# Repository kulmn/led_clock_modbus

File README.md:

# Clock with temperature sensor and wireless modbus protocol.

Hardware: 
- Schematic diagram (Autodesk EAGLE) in /schematic/ dir
- MCU: STM32F030K6
- Wireless: HC-12 module (433MHz)
- RTC: DS1338-33
- Indicator: 2.3 inch 7 segment led ( CA pin 1,5)

Firmvare:
- GCC Eclipse project, FreeRTOS, LibopenCM3

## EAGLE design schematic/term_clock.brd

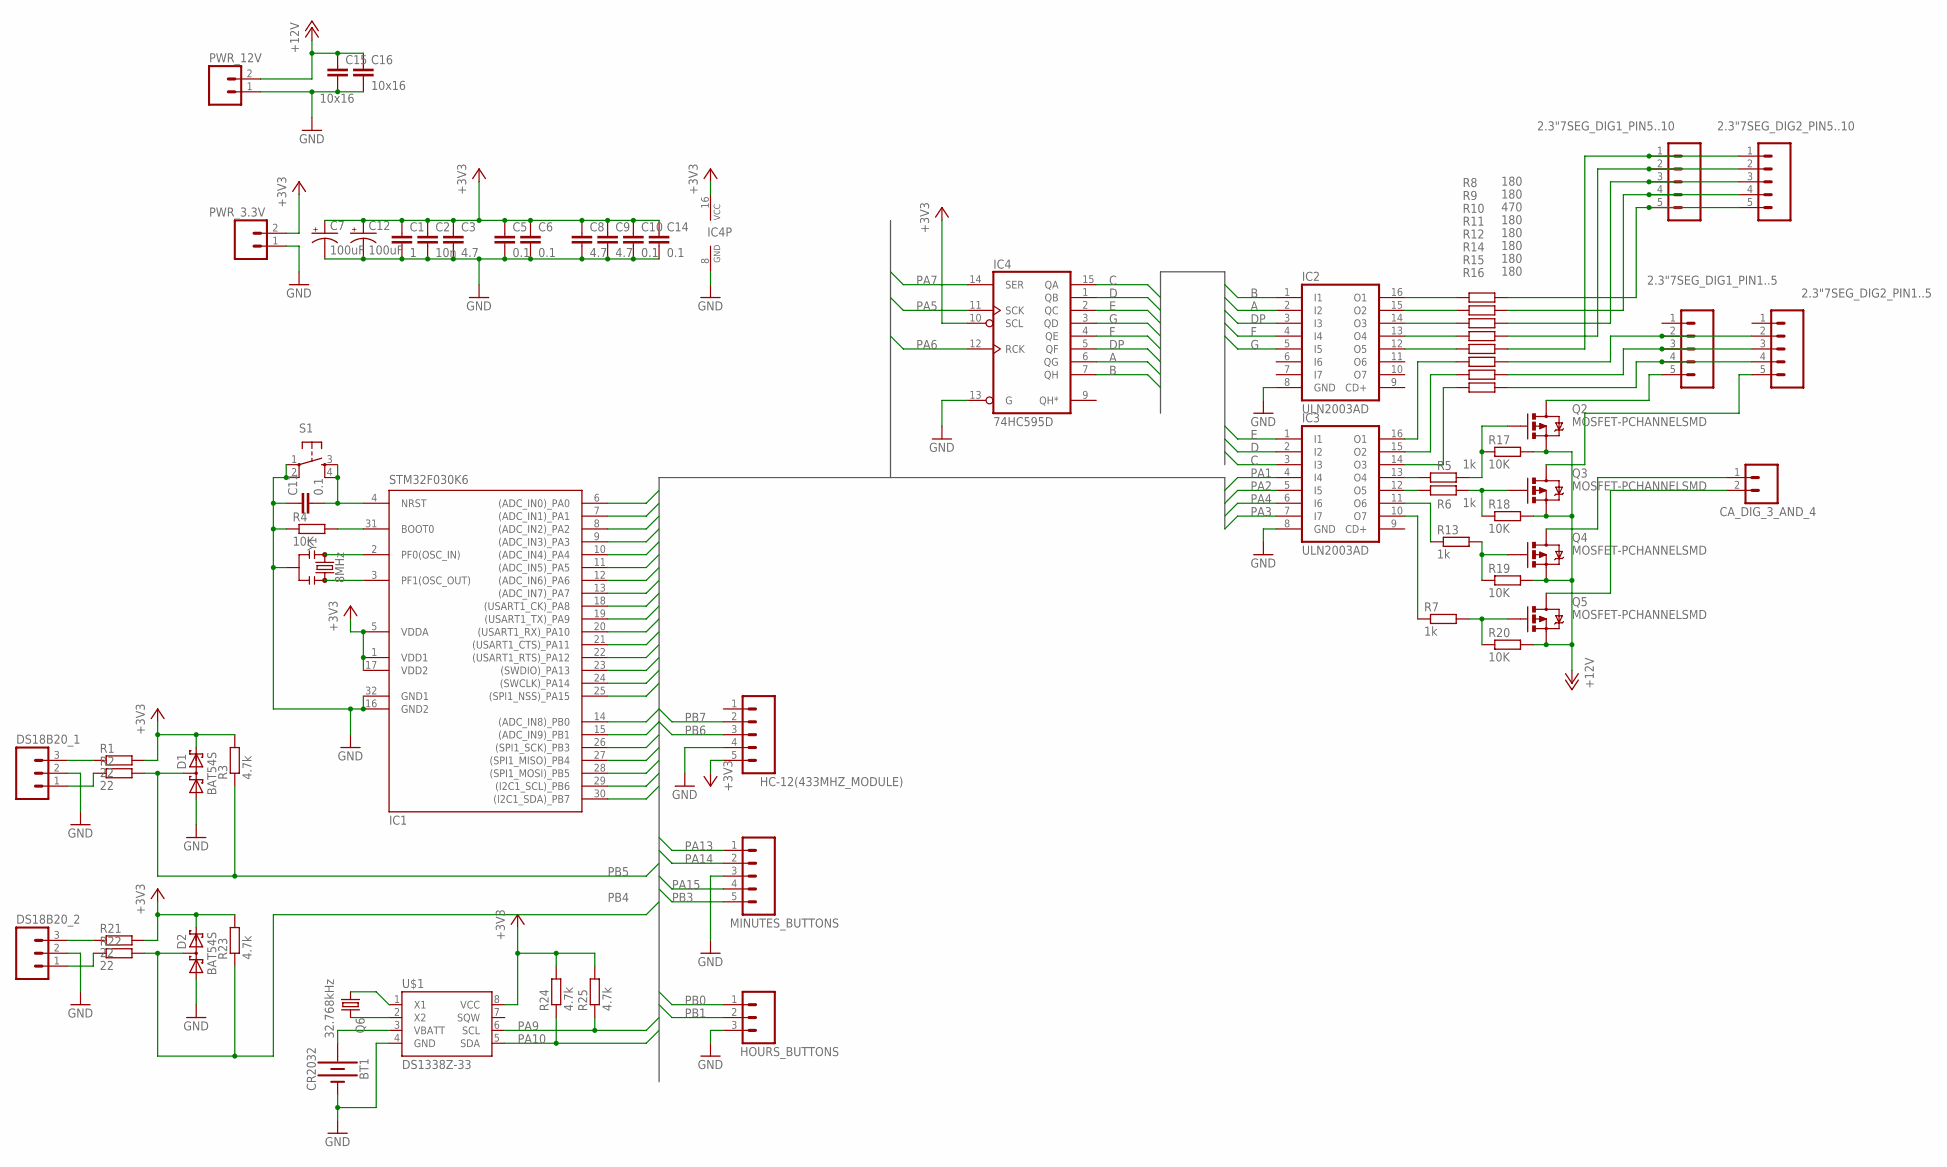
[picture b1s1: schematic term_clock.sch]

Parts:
2.3"7SEG_DIG1_PIN1..5, 2.3"7SEG_DIG1_PIN5..10, 2.3"7SEG_DIG2_PIN1..5, 2.3"7SEG_DIG2_PIN5..10: M05; 05P
BT1: CR2032; BATTCOM_20MM_PTH
C1: 1; C0805
C2: 10n; C0805
C3, C8, C9: 4.7; C0805
C5, C6, C10, C11, C14: 0.1; C0805
C7, C12: 100uF; EIA7343
C15, C16: 10x16; C1206
CA_DIG_3_AND_4: M02; 02P
D1, D2: BAT54S; SOT23
DS18B20_1, DS18B20_2: M03; 03P
HC-12(433MHZ_MODULE): M05; 05P
HOURS_BUTTONS: M03; 03P
IC1: STM32F030K6; TQFP32-08
IC2, IC3: ULN2003AD; SO16
IC4: 74HC595D; SO16
MINUTES_BUTTONS: M05; 05P
PWR_3.3V, PWR_12V: M02; 02P
Q2, Q3, Q4, Q5: MOSFET-PCHANNELSMD; SOT23-3
Q6: 32.768kHz; TC38H
R1, R2, R21, R22: 22; R0805
R3, R23, R24, R25: 4.7k; R0805
R4: 10K; R0805
R5, R6, R7, R13: 1k; R0603
R8, R9, R11, R12, R14, R15, R16: 180; R1206
R10: 470; R1206
R17, R18, R19, R20: 10K; R0603
S1: TAC_SWITCHSMD; TACTILE_SWITCH_SMD
U$1: DS1338Z-33; SO08
Y1: 8MHz; RESONATOR-SMD-3.2X1.3

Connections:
+3V3: C1.1, C2.1, C3.1, C5.1, C6.1, C7.A (+), C8.1, C9.1, C10.1, C12.A (+), C14.1, D1.2 (C2), D2.2 (C2), HC-12(433MHZ_MODULE).5, IC1.1 (VDD1), IC1.5 (VDDA), IC1.17 (VDD2), IC4.10 (SCL), IC4.16 (VCC), PWR_3.3V.2, R1.2, R3.2, R21.2, R23.2, R24.2, R25.2, U$1.8 (VCC)
+12V: C15.1, C16.1, PWR_12V.2, Q2.2 (S), Q3.2 (S), Q4.2 (S), Q5.2 (S), R17.2, R18.2, R19.2, R20.2
A: IC2.2 (I2), IC4.6 (QG)
B: IC2.1 (I1), IC4.7 (QH)
C: IC3.3 (I3), IC4.15 (QA)
D: IC3.2 (I2), IC4.1 (QB)
DP: IC2.3 (I3), IC4.5 (QF)
E: IC3.1 (I1), IC4.2 (QC)
F: IC2.4 (I4), IC4.4 (QE)
G: IC2.5 (I5), IC4.3 (QD)
GND: BT1.2 (-), C1.2, C2.2, C3.2, C5.2, C6.2, C7.C (-), C8.2, C9.2, C10.2, C11.1, C12.C (-), C14.2, C15.2, C16.2, D1.1 (A1), D2.1 (A1), DS18B20_1.2, DS18B20_2.2, HC-12(433MHZ_MODULE).4, HOURS_BUTTONS.3, IC1.16 (GND2), IC1.32 (GND1), IC2.8 (GND), IC3.8 (GND), IC4.8 (GND), IC4.13 (G), MINUTES_BUTTONS.3, PWR_3.3V.1, PWR_12V.1, R4.1, S1.1, S1.2, U$1.4 (GND), Y1.2
unnamed: DS18B20_1.3, R1.1
unnamed: IC1.2 (PF0(OSC_IN)), Y1.1
unnamed: IC1.3 (PF1(OSC_OUT)), Y1.3
unnamed: DS18B20_1.1, R2.1
unnamed: DS18B20_2.3, R21.1
unnamed: IC1.31 (BOOT0), R4.2
unnamed: DS18B20_2.1, R22.1
unnamed: Q6.2, U$1.2 (X2)
unnamed: Q6.1, U$1.1 (X1)
unnamed: BT1.1 (+), U$1.3 (VBATT)
unnamed: C11.2, IC1.4 (NRST), S1.3, S1.4
unnamed: IC2.16 (O1), R8.1
unnamed: IC2.15 (O2), R9.1
unnamed: IC2.14 (O3), R10.1
unnamed: IC2.13 (O4), R11.1
unnamed: IC2.12 (O5), R12.1
unnamed: Q3.1 (G), R6.2, R18.1
unnamed: Q4.1 (G), R13.2, R19.1
unnamed: Q5.1 (G), R7.2, R20.1
unnamed: 2.3"7SEG_DIG2_PIN1..5.5, Q3.3 (D)
unnamed: CA_DIG_3_AND_4.1, Q4.3 (D)
unnamed: CA_DIG_3_AND_4.2, Q5.3 (D)
unnamed: 2.3"7SEG_DIG1_PIN5..10.5, 2.3"7SEG_DIG2_PIN5..10.5, R8.2
unnamed: 2.3"7SEG_DIG1_PIN5..10.4, 2.3"7SEG_DIG2_PIN5..10.4, R9.2
unnamed: 2.3"7SEG_DIG1_PIN5..10.3, 2.3"7SEG_DIG2_PIN5..10.3, R10.2
unnamed: 2.3"7SEG_DIG1_PIN5..10.2, 2.3"7SEG_DIG2_PIN5..10.2, R11.2
unnamed: 2.3"7SEG_DIG1_PIN5..10.1, 2.3"7SEG_DIG2_PIN5..10.1, R12.2
unnamed: 2.3"7SEG_DIG1_PIN1..5.5, Q2.3 (D)
unnamed: 2.3"7SEG_DIG1_PIN1..5.2, 2.3"7SEG_DIG2_PIN1..5.2, R14.2
unnamed: 2.3"7SEG_DIG1_PIN1..5.3, 2.3"7SEG_DIG2_PIN1..5.3, R15.2
unnamed: 2.3"7SEG_DIG1_PIN1..5.4, 2.3"7SEG_DIG2_PIN1..5.4, R16.2
unnamed: IC3.10 (O7), R7.1
unnamed: IC3.11 (O6), R13.1
unnamed: IC3.12 (O5), R6.1
unnamed: Q2.1 (G), R5.2, R17.1
unnamed: IC3.13 (O4), R5.1
unnamed: IC3.16 (O1), R14.1
unnamed: IC3.15 (O2), R15.1
unnamed: IC3.14 (O3), R16.1
PA0: IC1.6 ((ADC_IN0)_PA0)
PA1: IC1.7 ((ADC_IN1)_PA1), IC3.4 (I4)
PA2: IC1.8 ((ADC_IN2)_PA2), IC3.5 (I5)
PA3: IC1.9 ((ADC_IN3)_PA3), IC3.7 (I7)
PA4: IC1.10 ((ADC_IN4)_PA4), IC3.6 (I6)
PA5: IC1.11 ((ADC_IN5)_PA5), IC4.11 (SCK)
PA6: IC1.12 ((ADC_IN6)_PA6), IC4.12 (RCK)
PA7: IC1.13 ((ADC_IN7)_PA7), IC4.14 (SER)
PA8: IC1.18 ((USART1_CK)_PA8)
PA9: IC1.19 ((USART1_TX)_PA9), R25.1, U$1.6 (SCL)
PA10: IC1.20 ((USART1_RX)_PA10), R24.1, U$1.5 (SDA)
PA11: IC1.21 ((USART1_CTS)_PA11)
PA12: IC1.22 ((USART1_RTS)_PA12)
PA13: IC1.23 ((SWDIO)_PA13), MINUTES_BUTTONS.1
PA14: IC1.24 ((SWCLK)_PA14), MINUTES_BUTTONS.2
PA15: IC1.25 ((SPI1_NSS)_PA15), MINUTES_BUTTONS.4
PB0: HOURS_BUTTONS.1, IC1.14 ((ADC_IN8)_PB0)
PB1: HOURS_BUTTONS.2, IC1.15 ((ADC_IN9)_PB1)
PB3: IC1.26 ((SPI1_SCK)_PB3), MINUTES_BUTTONS.5
PB4: D2.3 (C1A2), IC1.27 ((SPI1_MISO)_PB4), R22.2, R23.1
PB5: D1.3 (C1A2), IC1.28 ((SPI1_MOSI)_PB5), R2.2, R3.1
PB6: HC-12(433MHZ_MODULE).3, IC1.29 ((I2C1_SCL)_PB6)
PB7: HC-12(433MHZ_MODULE).2, IC1.30 ((I2C1_SDA)_PB7)

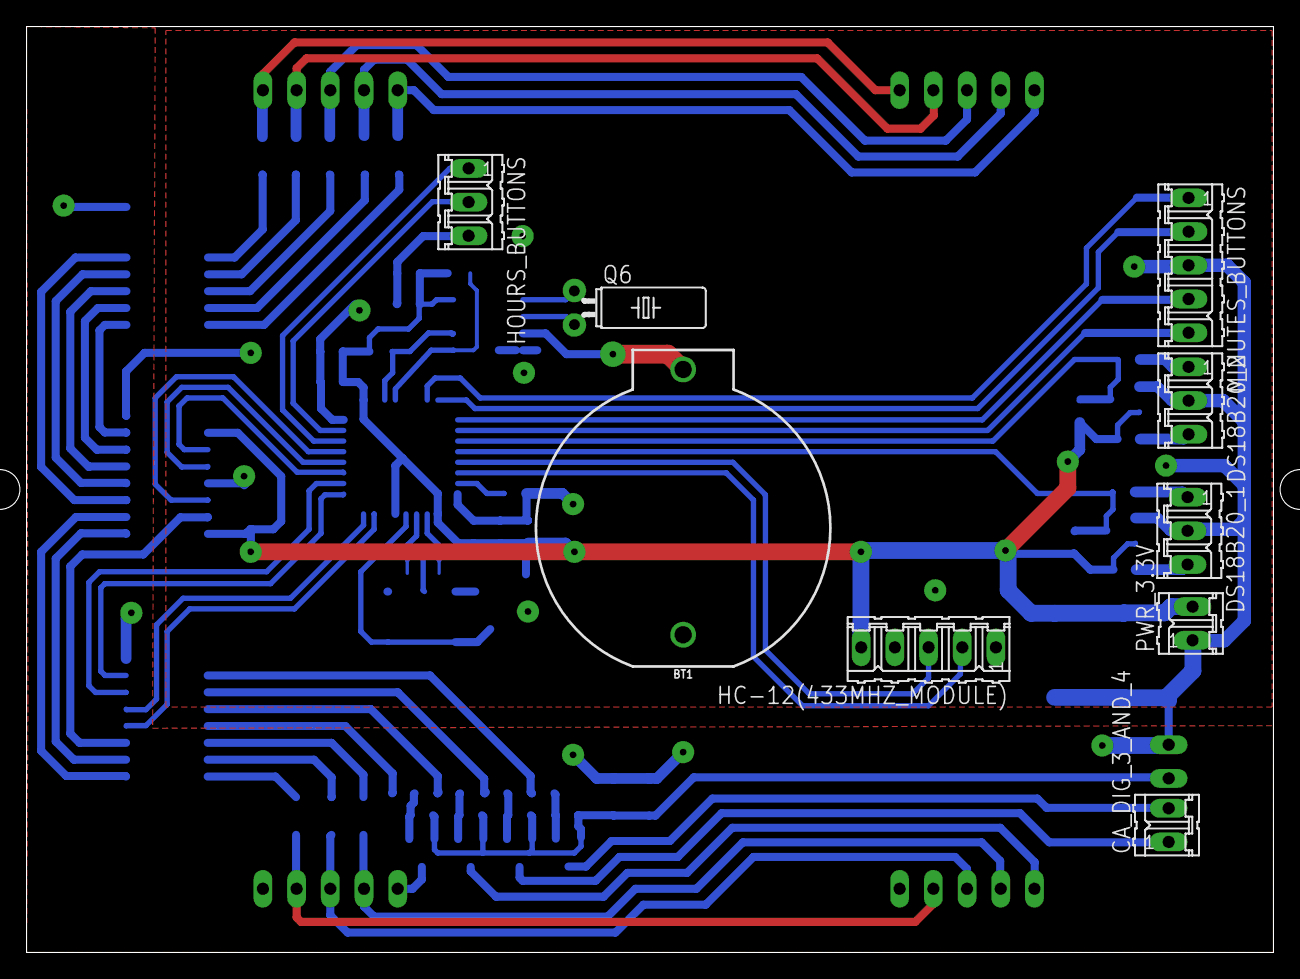
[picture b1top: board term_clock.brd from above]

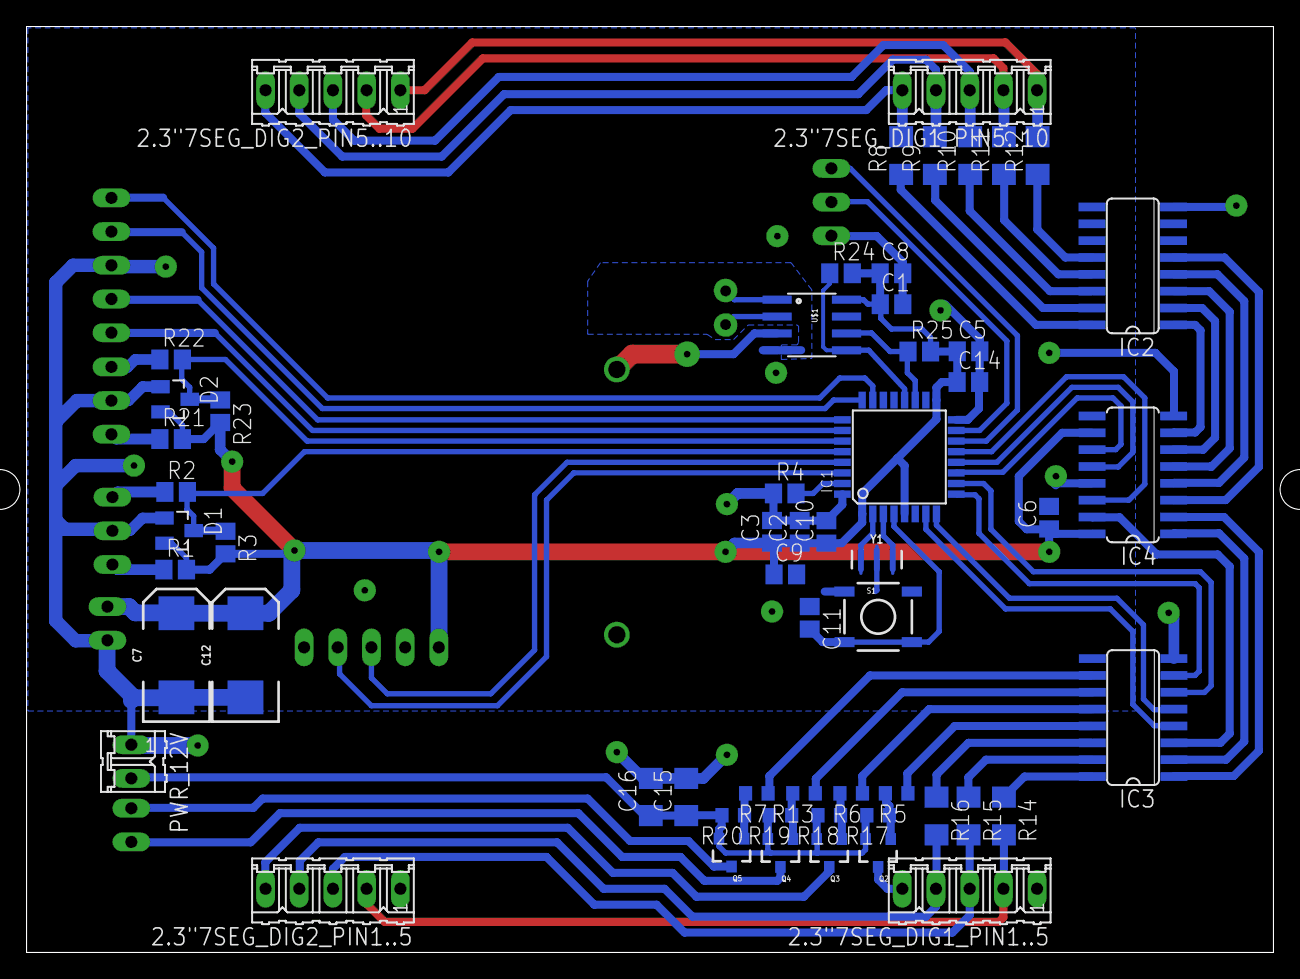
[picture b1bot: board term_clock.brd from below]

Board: 2 copper layers, 94.0 x 69.8 mm, 66 parts (57 on the bottom side), 69 nets.

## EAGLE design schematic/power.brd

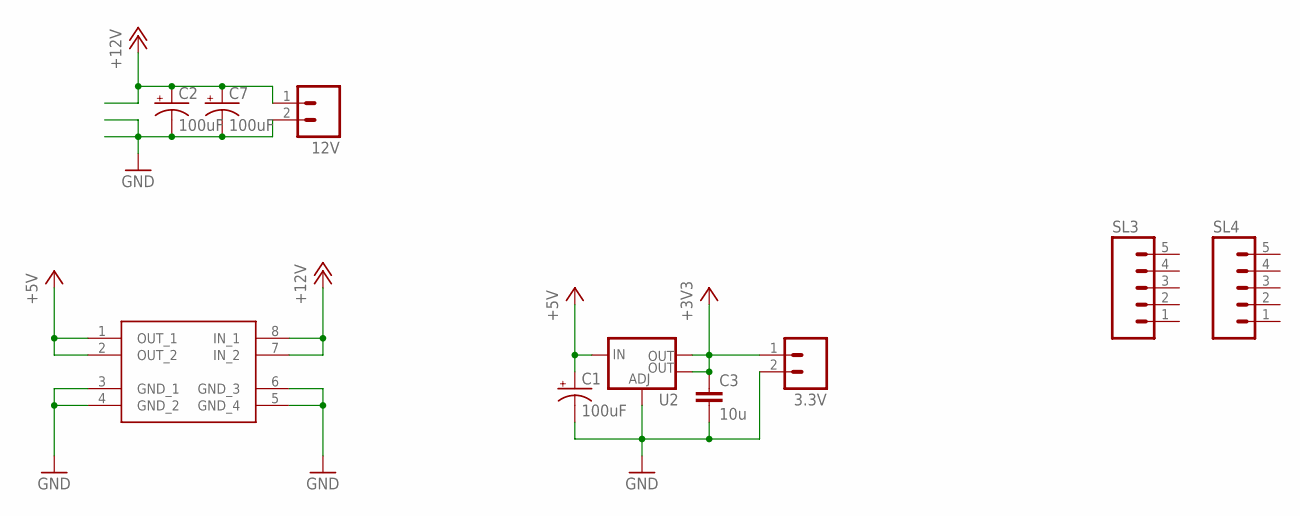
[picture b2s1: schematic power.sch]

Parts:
3.3V, 12V: M02; 02P
C1, C2, C7: 100uF; EIA7343
C3: 10u; C1206
SL3, SL4: M05; 05P
U2: V_REG_LM1117SOT223; SOT223
U$1: MP1584_MODUL

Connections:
+3V3: 3.3V.1, C3.1, U2.2 (OUT), U2.4 (OUT)
+5V: C1.A (+), U2.3 (IN), U$1.1 (OUT_1), U$1.2 (OUT_2)
+12V: 12V.1, C2.A (+), C7.A (+), U$1.7 (IN_2), U$1.8 (IN_1)
GND: 3.3V.2, 12V.2, C1.C (-), C2.C (-), C3.2, C7.C (-), U2.1 (ADJ), U$1.3 (GND_1), U$1.4 (GND_2), U$1.5 (GND_4), U$1.6 (GND_3)

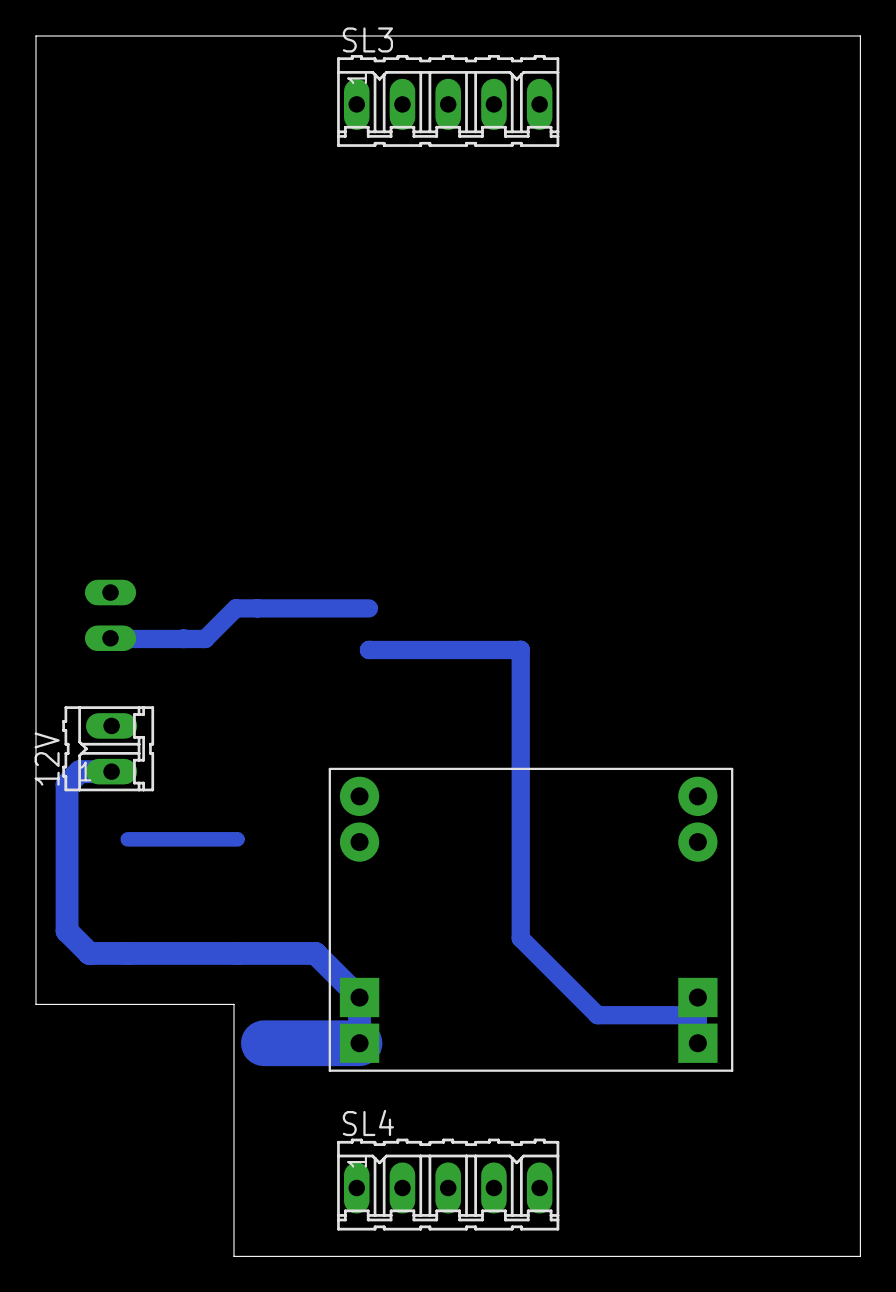
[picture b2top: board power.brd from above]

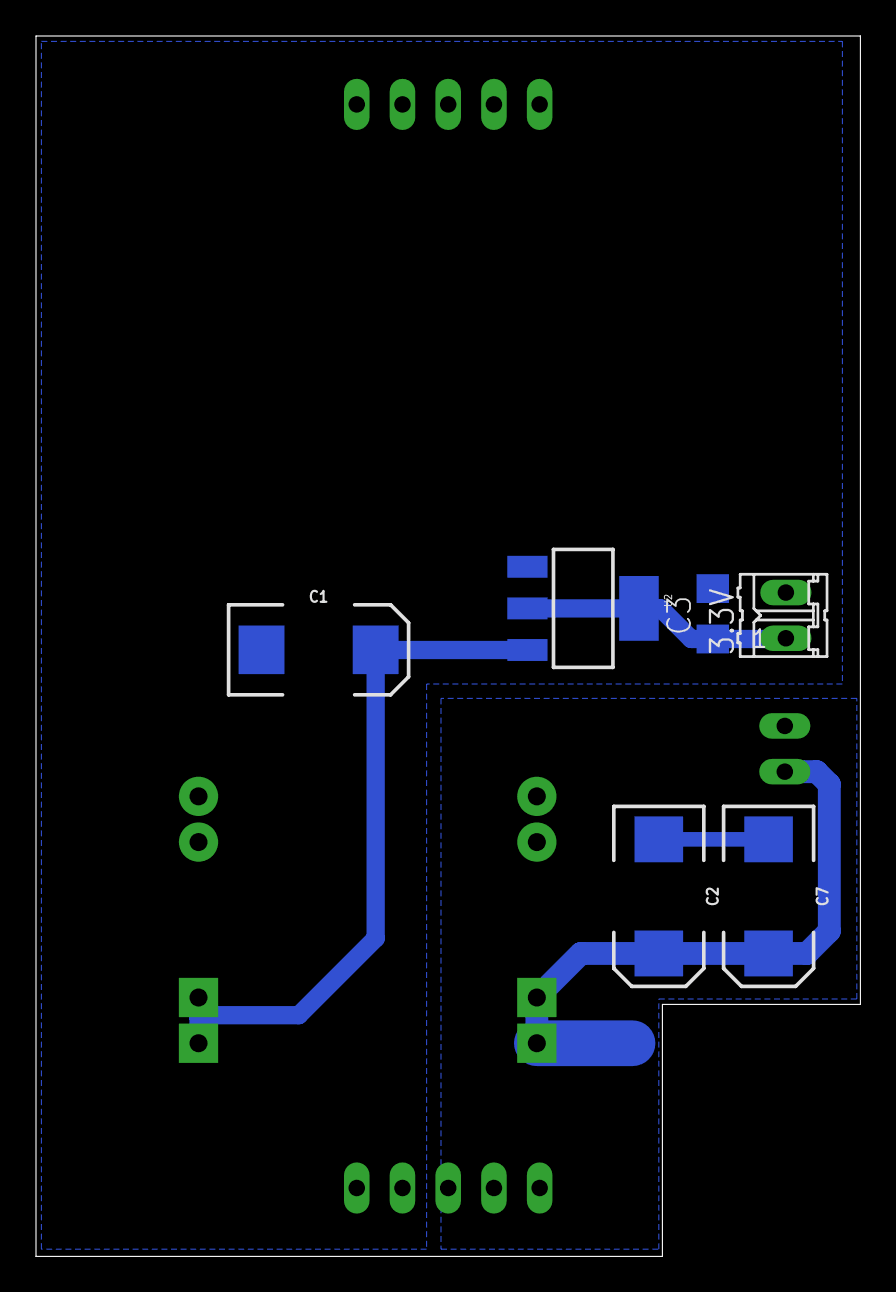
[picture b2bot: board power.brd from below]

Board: 2 copper layers, 45.8 x 67.8 mm, 10 parts (6 on the bottom side), 4 nets.

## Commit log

2020-01-04 init
2020-01-05 change project name
2020-05-06 rewrite freemodbus
    delete mb_close_port function
    delete eMBClose function
    usSndBufferCount -> local
    delete commented function
    eSndState -> MB_Serial_Driver
    xMBRTUTimerT35Expired -> driver
2020-05-06 add modbus time receive
2020-05-08 update clock from modbus (+/- 100 min), remove unused.
2020-05-08 mb var init
2020-05-10 release V1.0
2020-05-12 fix blinking
2020-11-30 add show date
2020-12-01 modbus protocol -> optional (USE_MODBUS define)
2020-12-01 add date change
2021-03-01 Add schematic
2021-03-01 Create LICENSE

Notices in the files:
parts and their libraries:
SparkFun-IC-Power: Licensing: Creative Commons ShareAlike 4.0 International - https://creativecommons.org/licenses/by-sa/4.0
SparkFun: Licensing: CC v3.0 Share-Alike You are welcome to use this library for commercial purposes.
